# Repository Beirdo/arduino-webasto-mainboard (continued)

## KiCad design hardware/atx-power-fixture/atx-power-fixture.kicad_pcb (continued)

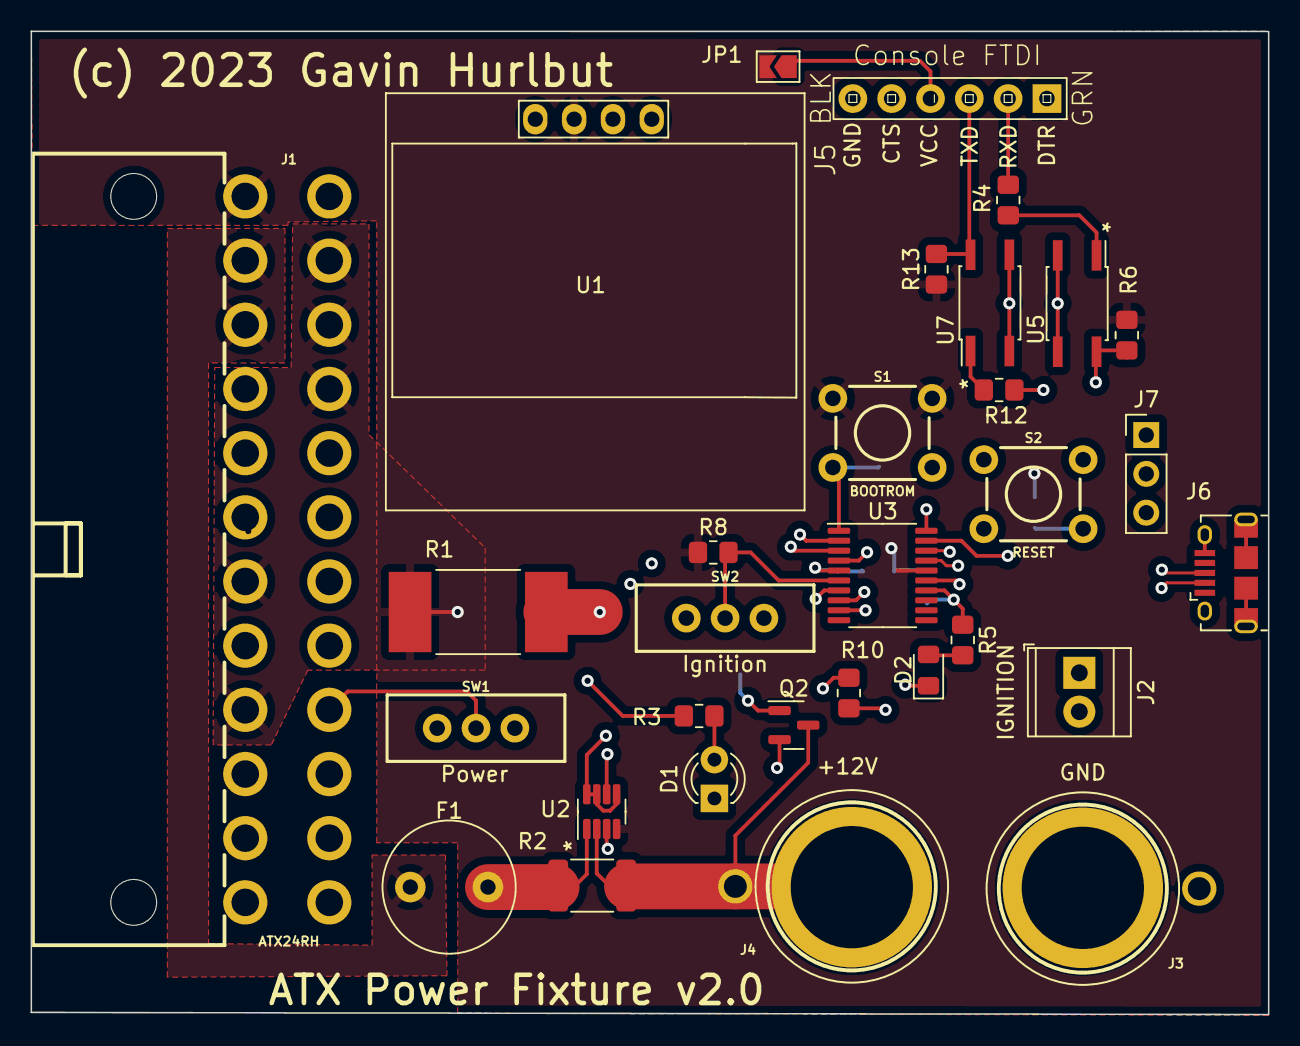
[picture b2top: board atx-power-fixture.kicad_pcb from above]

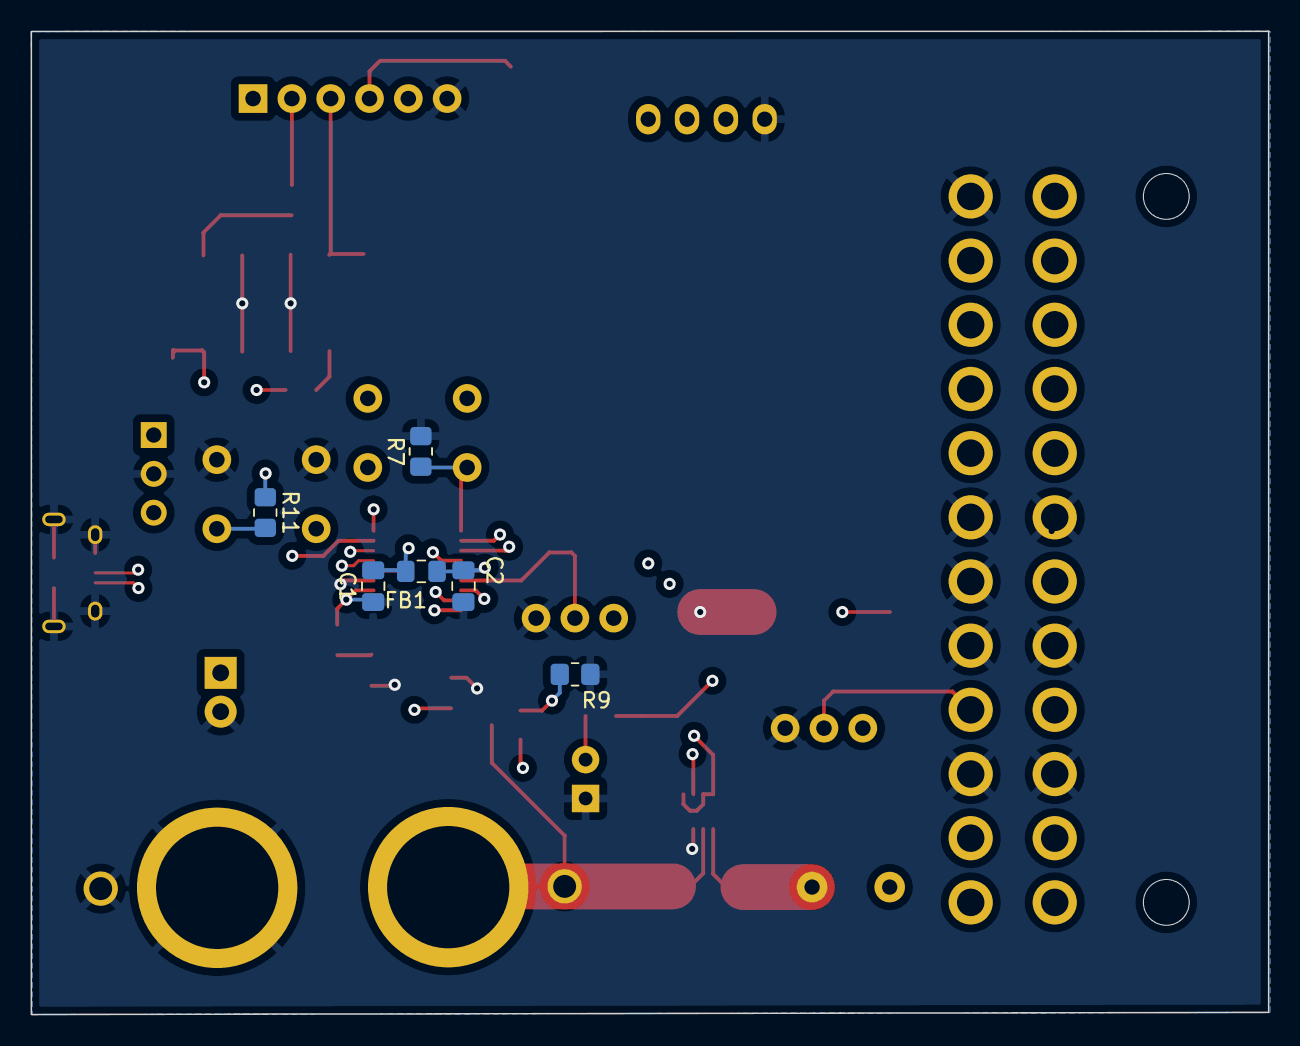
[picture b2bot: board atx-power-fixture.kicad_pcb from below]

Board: 4 copper layers, 81.0 x 64.3 mm, 37 parts (6 on the bottom side), 30 nets.

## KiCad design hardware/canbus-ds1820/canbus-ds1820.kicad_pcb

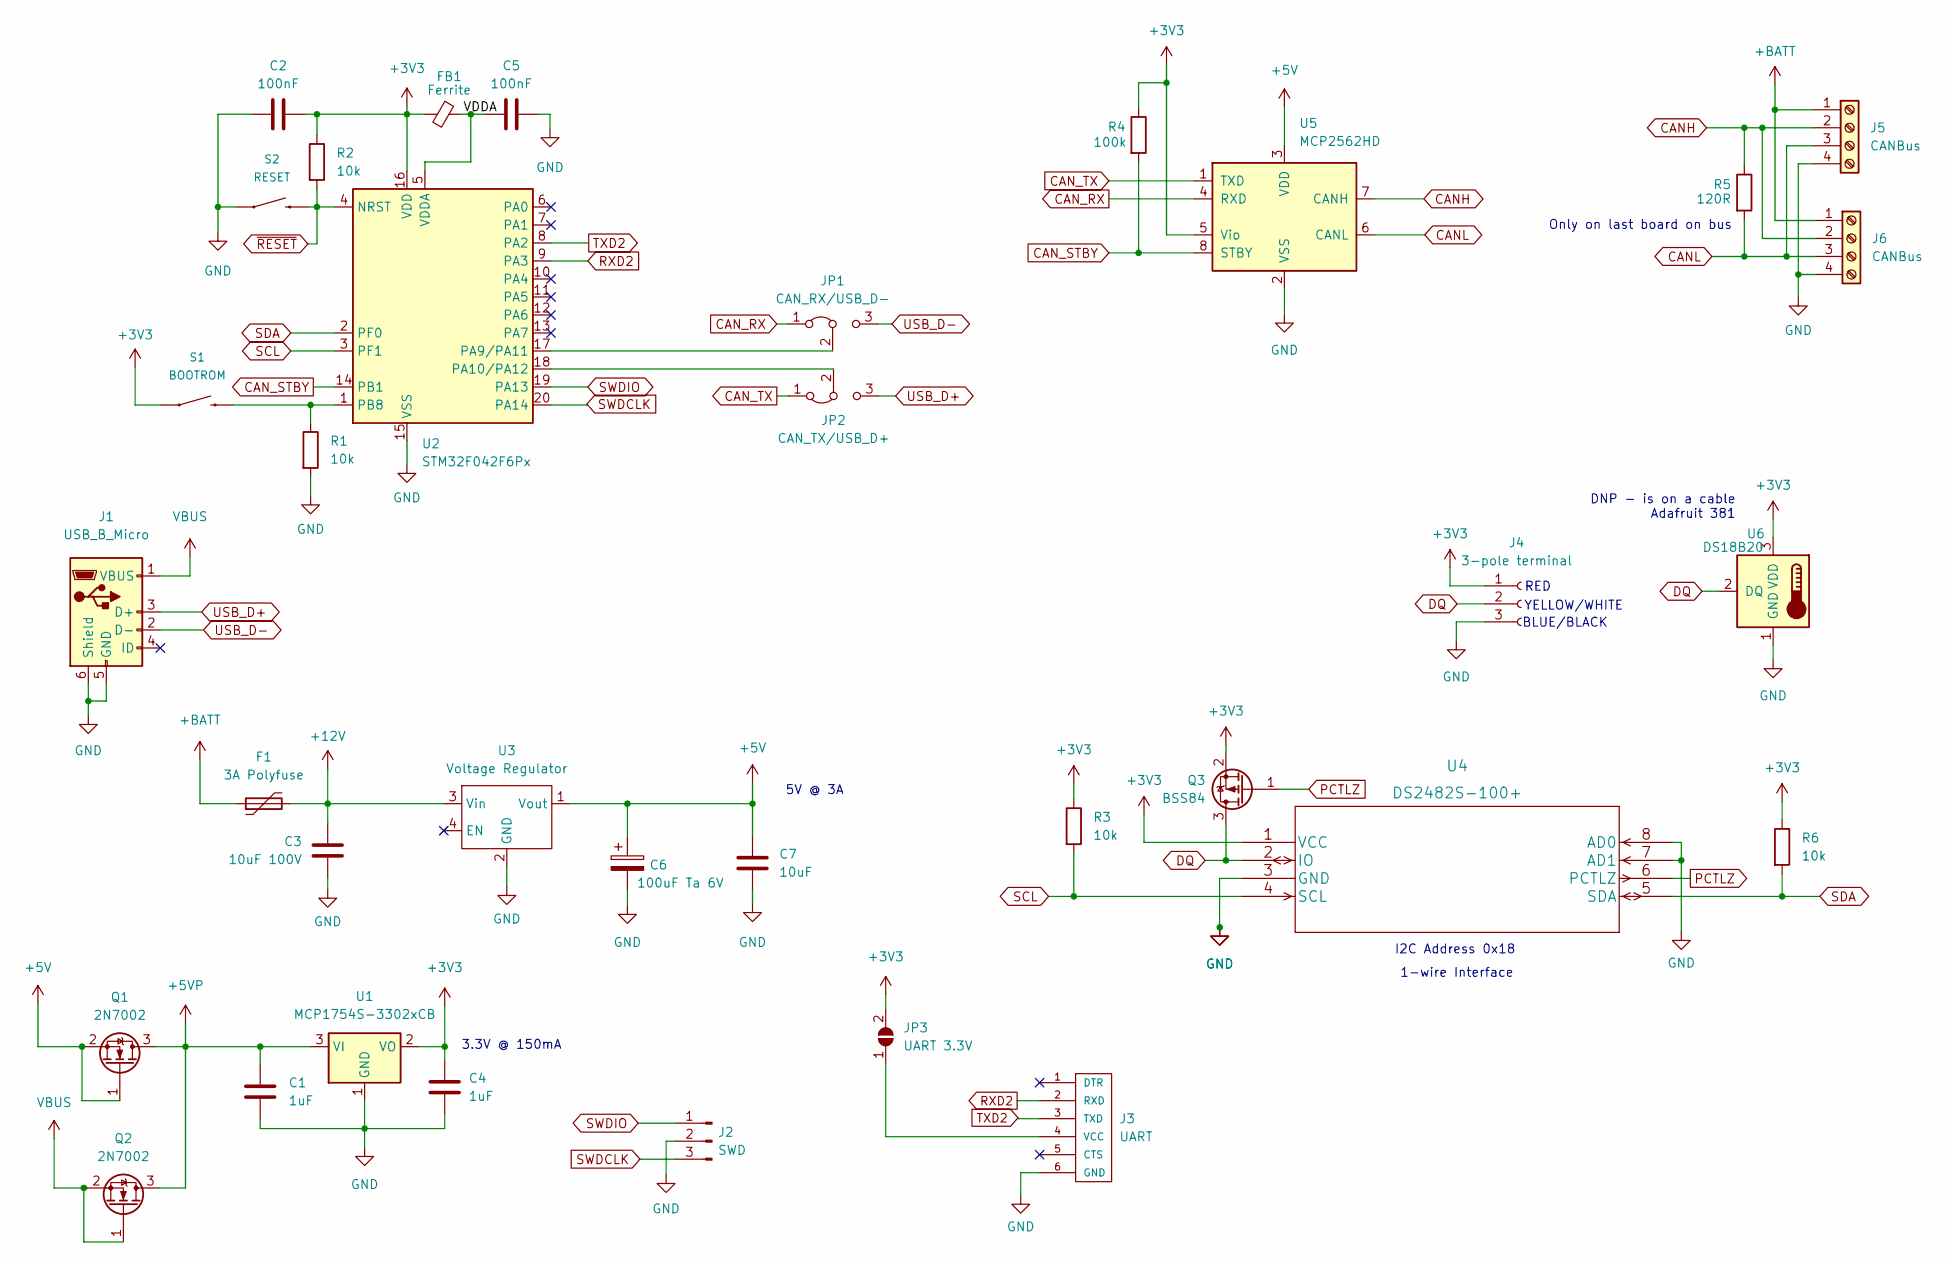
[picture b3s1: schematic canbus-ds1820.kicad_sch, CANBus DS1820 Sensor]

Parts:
C1, C4: 1uF; C_0805_2012Metric_Pad1.18x1.45mm_HandSolder
C2, C5: 100nF; C_0805_2012Metric_Pad1.18x1.45mm_HandSolder
C3: 10uF 100V; C_1210_3225Metric_Pad1.33x2.70mm_HandSolder
C6: 100uF Ta 6V; CP_EIA-3216-10_Kemet-I_Pad1.58x1.35mm_HandSolder
C7: 10uF; C_0805_2012Metric_Pad1.18x1.45mm_HandSolder
F1: 3A Polyfuse; R_1812_4532Metric_Pad1.30x3.40mm_HandSolder; Digikey F2772CT-ND
FB1: Ferrite; L_0805_2012Metric_Pad1.15x1.40mm_HandSolder
J1: USB_B_Micro; USB_Micro-B_Amphenol_10118194_Horizontal
J2: SWD; PinHeader_1x03_P2.54mm_Vertical
J3: UART; FTDI-TARGET
J4: 3-pole terminal; TerminalBlock_TE_282834-3_1x03_P2.54mm_Horizontal
J5, J6: CANBus; TerminalBlock_TE_282834-4_1x04_P2.54mm_Horizontal
JP1: CAN_RX/USB_D-; PinHeader_1x03_P2.54mm_Vertical
JP2: CAN_TX/USB_D+; PinHeader_1x03_P2.54mm_Vertical
JP3: UART 3.3V; SolderJumper-2_P1.3mm_Open_TrianglePad1.0x1.5mm
Q1, Q2: 2N7002; SOT-23
Q3: BSS84; SOT-23
R1, R2, R3, R6: 10k; R_0805_2012Metric_Pad1.20x1.40mm_HandSolder
R4: 100k; R_0805_2012Metric_Pad1.20x1.40mm_HandSolder
R5: 120R; R_0805_2012Metric_Pad1.20x1.40mm_HandSolder
S1: BOOTROM; TACTILE_SWITCH_PTH_6.0MM
S2: RESET; TACTILE_SWITCH_PTH_6.0MM
U1: MCP1754S-3302xCB; SOT-23
U2: STM32F042F6Px; TSSOP-20_4.4x6.5mm_P0.65mm
U3: Voltage Regulator; Switching_Regulator_Module
U4: DS2482S-100+; DS2482S-100&plus_
U5: MCP2562HD; SOIC-8_3.9x4.9mm_P1.27mm
U6: DS18B20; TO-92_Inline

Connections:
+3V3: C2.2, C4.1, FB1.2, J4.1, JP3.2 (B), Q3.2 (S), R2.1, R3.1, R4.1, R6.1, S1.1, U1.2 (VO), U2.16 (VDD), U4.1 (VCC), U5.5 (Vio), U6.3 (VDD)
+5V: C6.1, C7.1, Q1.1 (G), Q1.2 (S), U3.1 (Vout), U5.3 (VDD)
+5VP: C1.1, Q1.3 (D), Q2.3 (D), U1.3 (VI)
+12V: C3.1, F1.2, U3.3 (Vin)
+BATT: F1.1, J5.1, J6.1
/VDDA: C5.1, FB1.1, U2.5 (VDDA)
CANH: J5.2, J6.2, R5.1, U5.7 (CANH)
CANL: J5.3, J6.3, R5.2, U5.6 (CANL)
CAN_RX: JP1.1 (A), U5.4 (RXD)
CAN_STBY: R4.2, U2.14 (PB1), U5.8 (STBY)
CAN_TX: JP2.1 (A), U5.1 (TXD)
DQ: J4.2, Q3.3 (D), U4.2 (IO), U6.2 (DQ)
GND: C1.2, C2.1, C3.2, C4.2, C5.2, C6.2, C7.2, J1.5 (GND), J1.6 (Shield), J2.2, J3.6 (GND), J4.3, J5.4, J6.4, R1.2, S2.1, U1.1 (GND), U2.15 (VSS), U3.2 (GND), U4.3 (GND), U4.7 (AD1), U4.8 (AD0), U5.2 (VSS), U6.1 (GND)
unnamed: J3.4 (VCC), JP3.1 (A)
unnamed: JP1.2 (C), U2.17 (PA9/PA11)
unnamed: JP2.2 (C), U2.18 (PA10/PA12)
unnamed: R1.1, S1.3 (2), U2.1 (PB8)
PCTLZ: Q3.1 (G), U4.6 (PCTLZ)
RXD2: J3.2 (RXD), U2.9 (PA3)
SCL: R3.2, U2.3 (PF1), U4.4 (SCL)
SDA: R6.2, U2.2 (PF0), U4.5 (SDA)
SWDCLK: J2.3, U2.20 (PA14)
SWDIO: J2.1, U2.19 (PA13)
TXD2: J3.3 (TXD), U2.8 (PA2)
USB_D+: J1.3 (D+), JP2.3 (B)
USB_D-: J1.2 (D-), JP1.3 (B)
VBUS: J1.1 (VBUS), Q2.1 (G), Q2.2 (S)
~RESET: R2.2, S2.3 (2), U2.4 (NRST)

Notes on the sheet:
5V @ 3A
Only on last board on bus
I2C Address 0x18
BLUE/BLACK
YELLOW/WHITE
RED
1-wire Interface
DNP - is on a cable Adafruit 381
3.3V @ 150mA

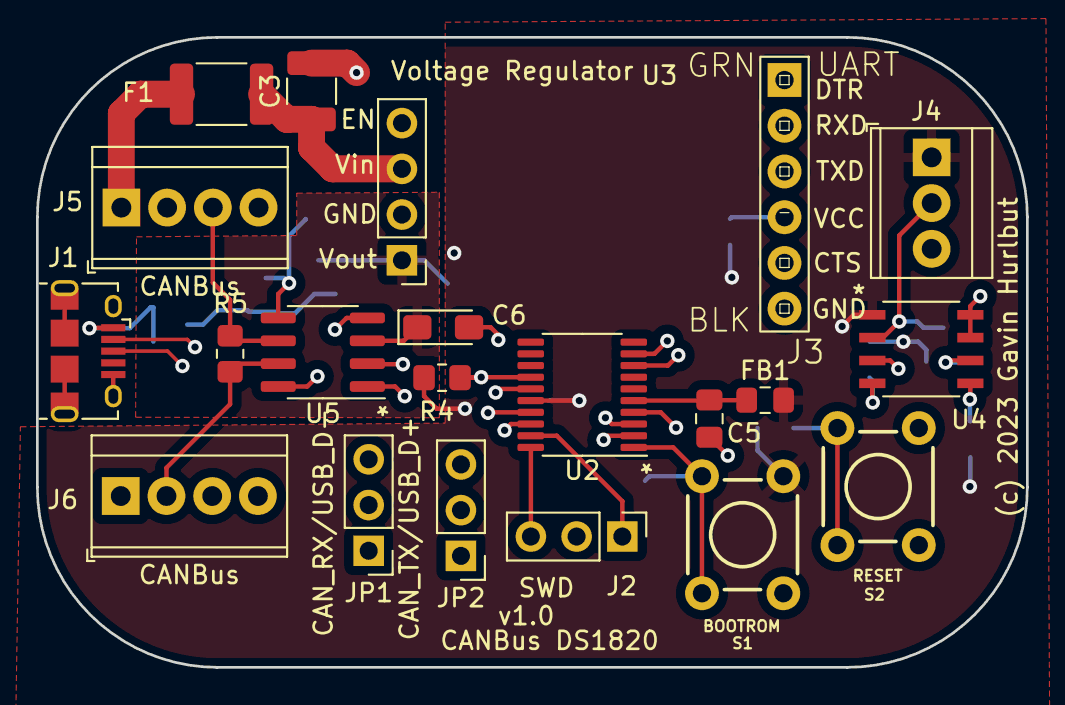
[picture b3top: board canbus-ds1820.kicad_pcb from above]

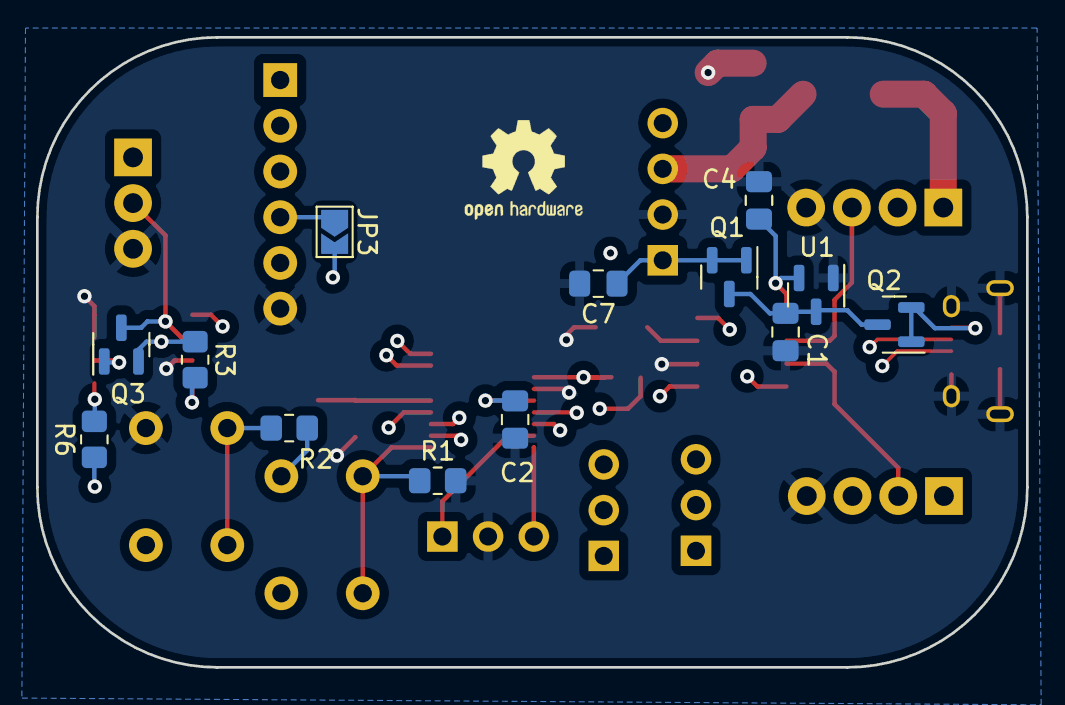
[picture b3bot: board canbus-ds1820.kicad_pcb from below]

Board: 4 copper layers, 55.0 x 35.0 mm, 35 parts (13 on the bottom side), 28 nets.

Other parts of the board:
BOARD: Altoid-Board-Outline

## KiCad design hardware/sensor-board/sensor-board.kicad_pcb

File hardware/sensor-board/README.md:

Coolant sensor:  PANW103395-395 (Digikey 570-1458-ND) inserted into:
                 https://www.amazon.com/dp/B09V6Y4ST8
	         set R6 = 10k, R4 = 0R, R7 = open

Battery voltage: set R6 = open, R4 = 49.9k 1%, R7 = 10.0k 1%

Exhaust sensor: K Type thermocouple

Ignition sensor: diode-protected input with pullup.  When ignition is on, 
                 the diode is reverse biased, and thus the input is high.
		 when ignition is on, the diode is forward biased, and the
                 input is low (around 0.7V).

Outdoors temp sensor:  DS18B20 on a cable - Adafruit part 381, connected to 
                       DS2482S-100+ 1Wire-I2C interface.

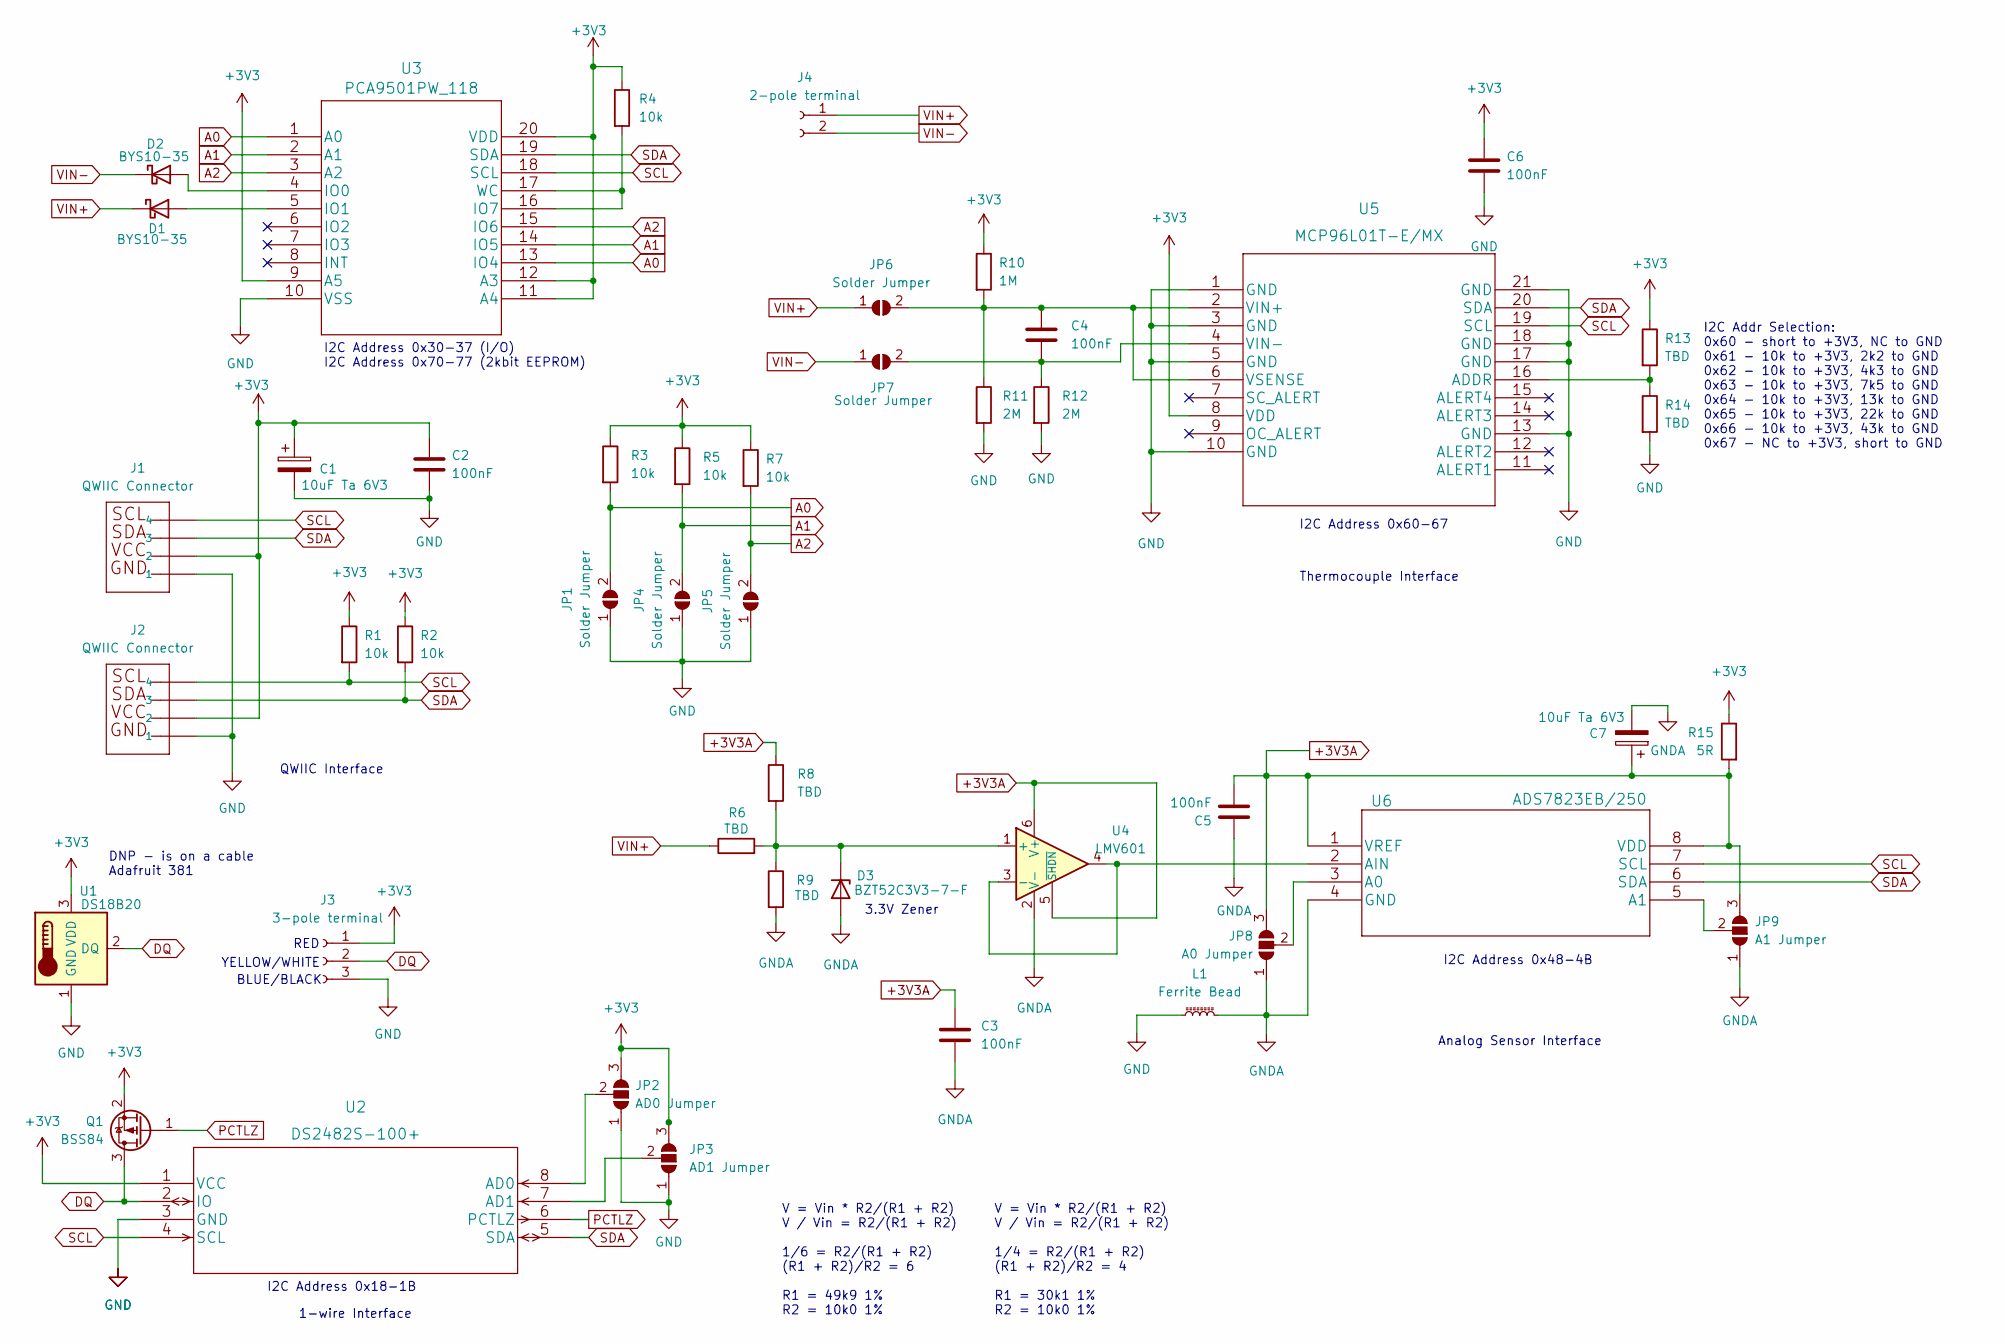
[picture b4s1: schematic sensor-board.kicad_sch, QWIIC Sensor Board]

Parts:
C1, C7: 10uF Ta 6V3; CP_EIA-3216-10_Kemet-I_Pad1.58x1.35mm_HandSolder
C2, C3, C4, C5, C6: 100nF; C_0805_2012Metric_Pad1.18x1.45mm_HandSolder
D1, D2: BYS10-35; D_SMA_Handsoldering
D3: BZT52C3V3-7-F; D_SOD-123
J1, J2: QWIIC Connector
J3: 3-pole terminal; TerminalBlock_Altech_AK300-3_P5.00mm
J4: 2-pole terminal; TerminalBlock_Altech_AK300-2_P5.00mm
JP1, JP4, JP5, JP6, JP7: Solder Jumper; SolderJumper-2_P1.3mm_Open_TrianglePad1.0x1.5mm
JP2: AD0 Jumper; SolderJumper-3_P2.0mm_Open_TrianglePad1.0x1.5mm
JP3: AD1 Jumper; SolderJumper-3_P2.0mm_Open_TrianglePad1.0x1.5mm
JP8: A0 Jumper; SolderJumper-3_P2.0mm_Open_TrianglePad1.0x1.5mm
JP9: A1 Jumper; SolderJumper-3_P2.0mm_Open_TrianglePad1.0x1.5mm
L1: Ferrite Bead; L_0805_2012Metric_Pad1.05x1.20mm_HandSolder
Q1: BSS84; SOT-23
R1, R2, R3, R4, R5, R7: 10k; R_0805_2012Metric_Pad1.20x1.40mm_HandSolder
R6, R8, R9, R13, R14: TBD; R_0805_2012Metric_Pad1.20x1.40mm_HandSolder
R10: 1M; R_0805_2012Metric_Pad1.20x1.40mm_HandSolder
R11, R12: 2M; R_0805_2012Metric_Pad1.20x1.40mm_HandSolder
R15: 5R; R_0805_2012Metric_Pad1.20x1.40mm_HandSolder
U1: DS18B20; TO-92_Inline
U2: DS2482S-100+; ds2482s-100&plus_
U3: PCA9501PW_118
U4: LMV601; SOT-363_SC-70-6
U5: MCP96L01T-E/MX; MCP96L01T-E&slash_MX
U6: ADS7823EB/250; ADS7823EB&slash_250

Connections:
+3V3: C1.1, C2.1, C6.1, J1.2, J2.2, J3.1, JP2.3 (B), JP3.3 (B), Q1.2 (S), R1.1, R2.1, R3.1, R4.1, R5.1, R7.1, R10.1, R13.1, R15.1, U1.3 (VDD), U2.1 (VCC), U3.9 (A5), U3.11 (A4), U3.12 (A3), U3.20 (VDD), U5.8 (VDD)
+3V3A: C3.2, C5.1, C7.1, JP8.3 (B), JP9.3 (B), R8.1, R15.2, U4.5 (~SHDN), U4.6 (V+), U6.1 (VREF), U6.8 (VDD)
A0: JP1.2 (B), R3.2, U3.1 (A0), U3.13 (IO4)
A1: JP4.2 (B), R5.2, U3.2 (A1), U3.14 (IO5)
A2: JP5.2 (B), R7.2, U3.3 (A2), U3.15 (IO6)
DQ: J3.2, Q1.3 (D), U1.2 (DQ), U2.2 (IO)
GND: C1.2, C2.2, C6.2, J1.1, J2.1, J3.3, JP1.1 (A), JP2.1 (A), JP3.1 (A), JP4.1 (A), JP5.1 (A), L1.1, R11.2, R12.2, R14.2, U1.1 (GND), U2.3 (GND), U3.10 (VSS), U5.1 (GND), U5.3 (GND), U5.5 (GND), U5.10 (GND), U5.13 (GND), U5.17 (GND), U5.18 (GND), U5.21 (GND)
GNDA: C3.1, C5.2, C7.2, D3.2 (A), JP8.1 (A), JP9.1 (A), L1.2, R9.2, U4.2 (V-), U6.4 (GND)
unnamed: C4.1, JP6.2 (B), R10.2, R11.1, U5.2 (VIN+), U5.6 (VSENSE)
unnamed: C4.2, JP7.2 (B), R12.1, U5.4 (VIN-)
unnamed: D3.1 (K), R6.2, R8.2, R9.1, U4.1 (+)
unnamed: JP2.2 (C), U2.8 (AD0)
unnamed: JP3.2 (C), U2.7 (AD1)
unnamed: JP8.2 (C), U6.3 (A0)
unnamed: JP9.2 (C), U6.5 (A1)
unnamed: R4.2, U3.16 (IO7), U3.17 (WC)
unnamed: R13.2, R14.1, U5.16 (ADDR)
unnamed: D2.2 (A), U3.4 (IO0)
unnamed: D1.2 (A), U3.5 (IO1)
unnamed: U4.3 (-), U4.4, U6.2 (AIN)
PCTLZ: Q1.1 (G), U2.6 (PCTLZ)
SCL: J1.4, J2.4, R1.2, U2.4 (SCL), U3.18 (SCL), U5.19 (SCL), U6.7 (SCL)
SDA: J1.3, J2.3, R2.2, U2.5 (SDA), U3.19 (SDA), U5.20 (SDA), U6.6 (SDA)
VIN+: D1.1 (K), J4.1, JP6.1 (A), R6.1
VIN-: D2.1 (K), J4.2, JP7.1 (A)

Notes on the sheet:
I2C Address 0x48-4B
YELLOW/WHITE
DNP - is on a cable Adafruit 381
BLUE/BLACK
V = Vin * R2/(R1 + R2) V / Vin = R2/(R1 + R2) 1/6 = R2/(R1 + R2) (R1 + R2)/R2 = 6 R1 = 49k9 1% R2 = 10k0 1%
I2C Address 0x30-37 (I/O) I2C Address 0x70-77 (2kbit EEPROM)
RED
I2C Address 0x18-1B
3.3V Zener
Thermocouple Interface
Analog Sensor Interface
QWIIC Interface
I2C Addr Selection: 0x60 - short to +3V3, NC to GND 0x61 - 10k to +3V3, 2k2 to GND 0x62 - 10k to +3V3, 4k3 to GND 0x63 - 10k to +3V3, 7k5 to GND 0x64 - 10k to +3V3, 13k to GND 0x65 - 10k to +3V3, 22k to GND 0x66 - 10k to +3V3, 43k to GND 0x67 - NC to +3V3, short to GND
V = Vin * R2/(R1 + R2) V / Vin = R2/(R1 + R2) 1/4 = R2/(R1 + R2) (R1 + R2)/R2 = 4 R1 = 30k1 1% R2 = 10k0 1%
1-wire Interface
I2C Address 0x60-67

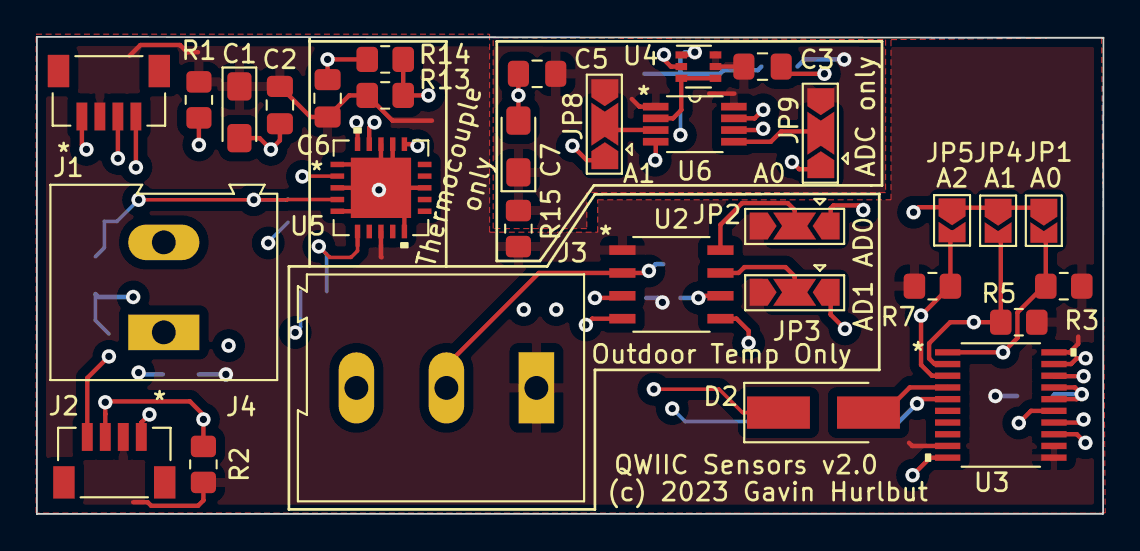
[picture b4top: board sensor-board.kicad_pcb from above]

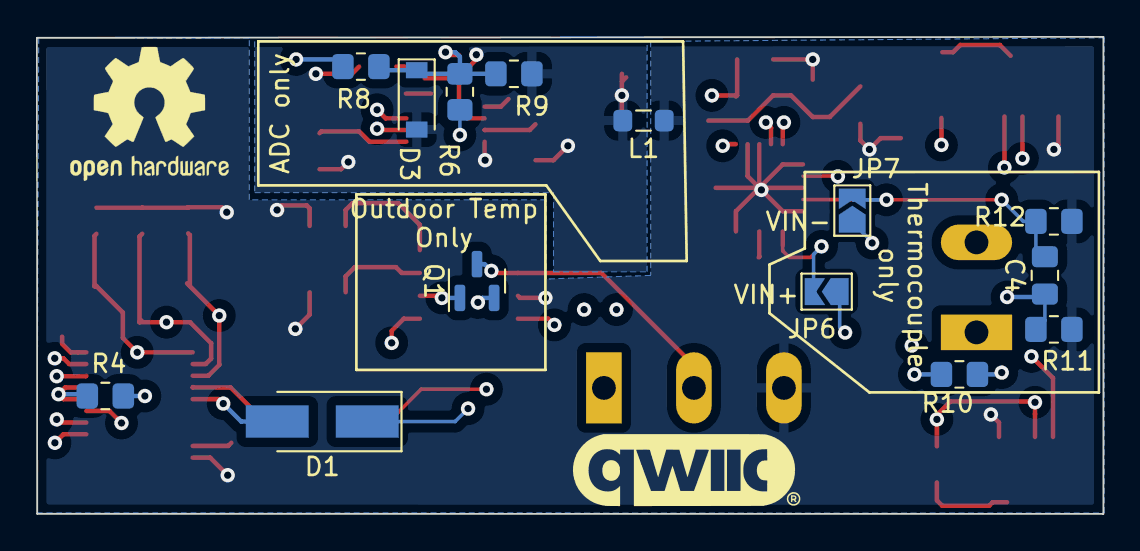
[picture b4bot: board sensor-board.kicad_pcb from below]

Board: 4 copper layers, 59.2 x 26.5 mm, 45 parts (14 on the bottom side), 25 nets.

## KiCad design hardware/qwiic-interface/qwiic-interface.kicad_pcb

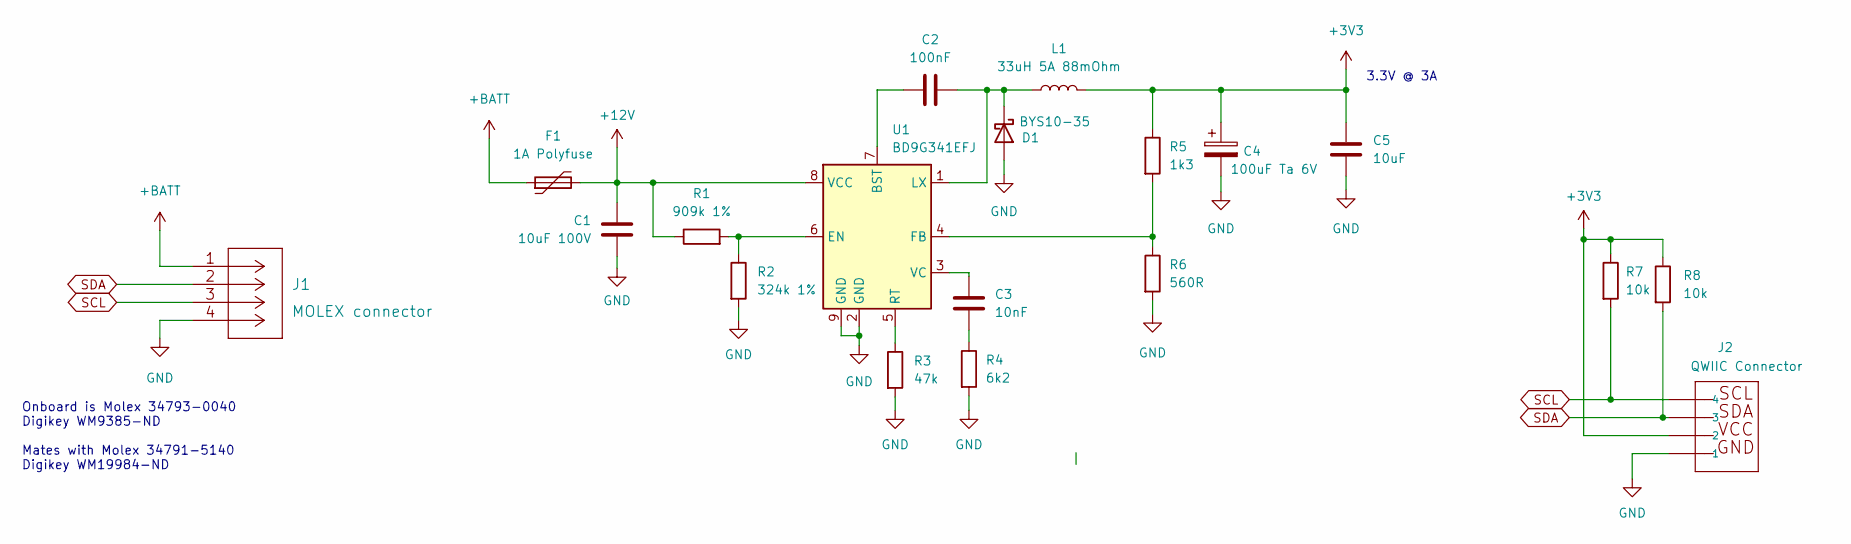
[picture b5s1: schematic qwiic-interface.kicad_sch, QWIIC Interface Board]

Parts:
C1: 10uF 100V; C_1210_3225Metric_Pad1.33x2.70mm_HandSolder
C2: 100nF; C_0805_2012Metric_Pad1.18x1.45mm_HandSolder
C3: 10nF; C_0805_2012Metric_Pad1.18x1.45mm_HandSolder
C4: 100uF Ta 6V; CP_EIA-3216-10_Kemet-I_Pad1.58x1.35mm_HandSolder
C5: 10uF; C_0805_2012Metric_Pad1.18x1.45mm_HandSolder
D1: BYS10-35; D_SMA_Handsoldering
F1: 1A Polyfuse; R_0805_2012Metric_Pad1.20x1.40mm_HandSolder; Digikey F2772CT-ND
J1: MOLEX connector; 347930040
J2: QWIIC Connector
L1: 33uH 5A 88mOhm; PM4346.333NLT; Digikey 553-PM4346.333NLTTR-ND
R1: 909k 1%; R_0805_2012Metric_Pad1.20x1.40mm_HandSolder
R2: 324k 1%; R_0805_2012Metric_Pad1.20x1.40mm_HandSolder
R3: 47k; R_0805_2012Metric_Pad1.20x1.40mm_HandSolder
R4: 6k2; R_0805_2012Metric_Pad1.20x1.40mm_HandSolder
R5: 1k3; R_0805_2012Metric_Pad1.20x1.40mm_HandSolder
R6: 560R; R_0805_2012Metric_Pad1.20x1.40mm_HandSolder
R7, R8: 10k; R_0805_2012Metric_Pad1.20x1.40mm_HandSolder
U1: BD9G341EFJ; HTSOP-8-1EP_3.9x4.9mm_P1.27mm_EP2.4x3.2mm_ThermalVias

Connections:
+3V3: C4.1, C5.1, J2.2, L1.2, R5.1, R7.1, R8.1
+12V: C1.1, F1.2, R1.1, U1.8 (VCC)
+BATT: F1.1, J1.1
GND: C1.2, C4.2, C5.2, D1.2 (A), J1.4, J2.1, R2.2, R3.2, R4.2, R6.2, U1.2 (GND), U1.9 (GND)
unnamed: C2.1, U1.7 (BST)
unnamed: C2.2, D1.1 (K), L1.1, U1.1 (LX)
unnamed: C3.1, U1.3 (VC)
unnamed: C3.2, R4.1
unnamed: R1.2, R2.1, U1.6 (EN)
unnamed: R3.1, U1.5 (RT)
unnamed: R5.2, R6.1, U1.4 (FB)
SCL: J1.3, J2.4, R7.2
SDA: J1.2, J2.3, R8.2

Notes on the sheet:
Onboard is Molex 34793-0040 Digikey WM9385-ND Mates with Molex 34791-5140 Digikey WM19984-ND
3.3V @ 3A

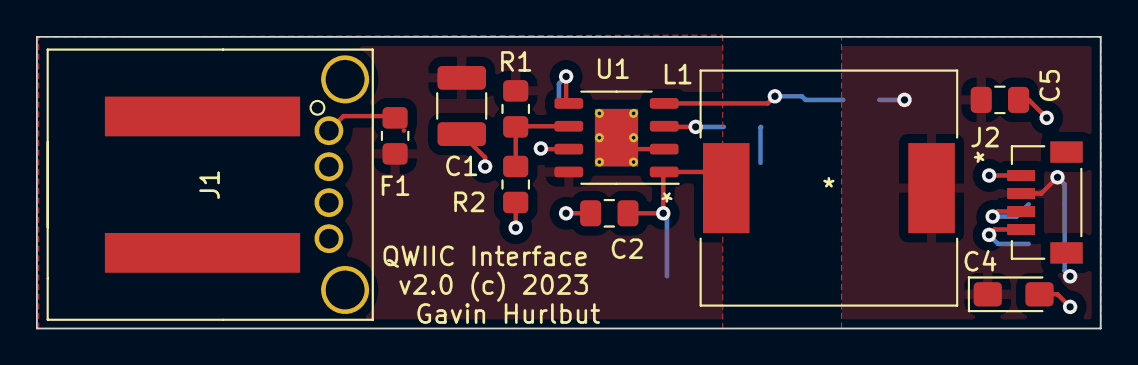
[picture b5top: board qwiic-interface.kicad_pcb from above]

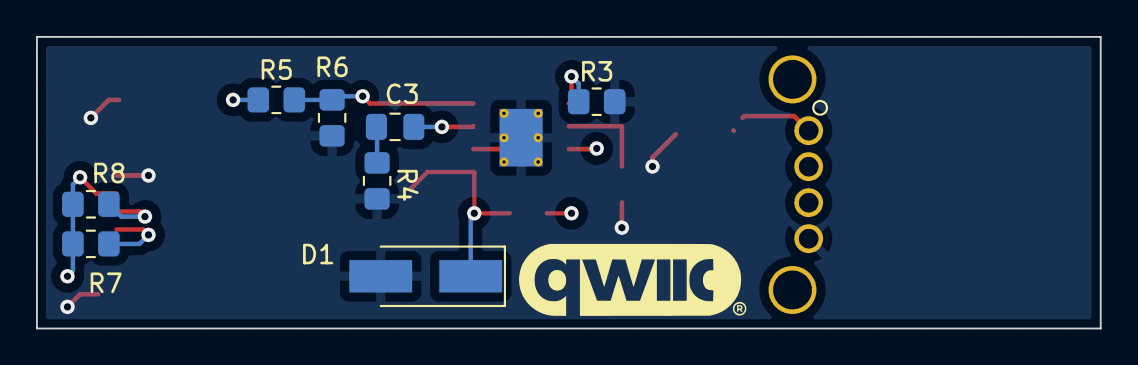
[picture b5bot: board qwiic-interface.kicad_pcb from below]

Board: 4 copper layers, 59.1 x 16.2 mm, 19 parts (8 on the bottom side), 13 nets.

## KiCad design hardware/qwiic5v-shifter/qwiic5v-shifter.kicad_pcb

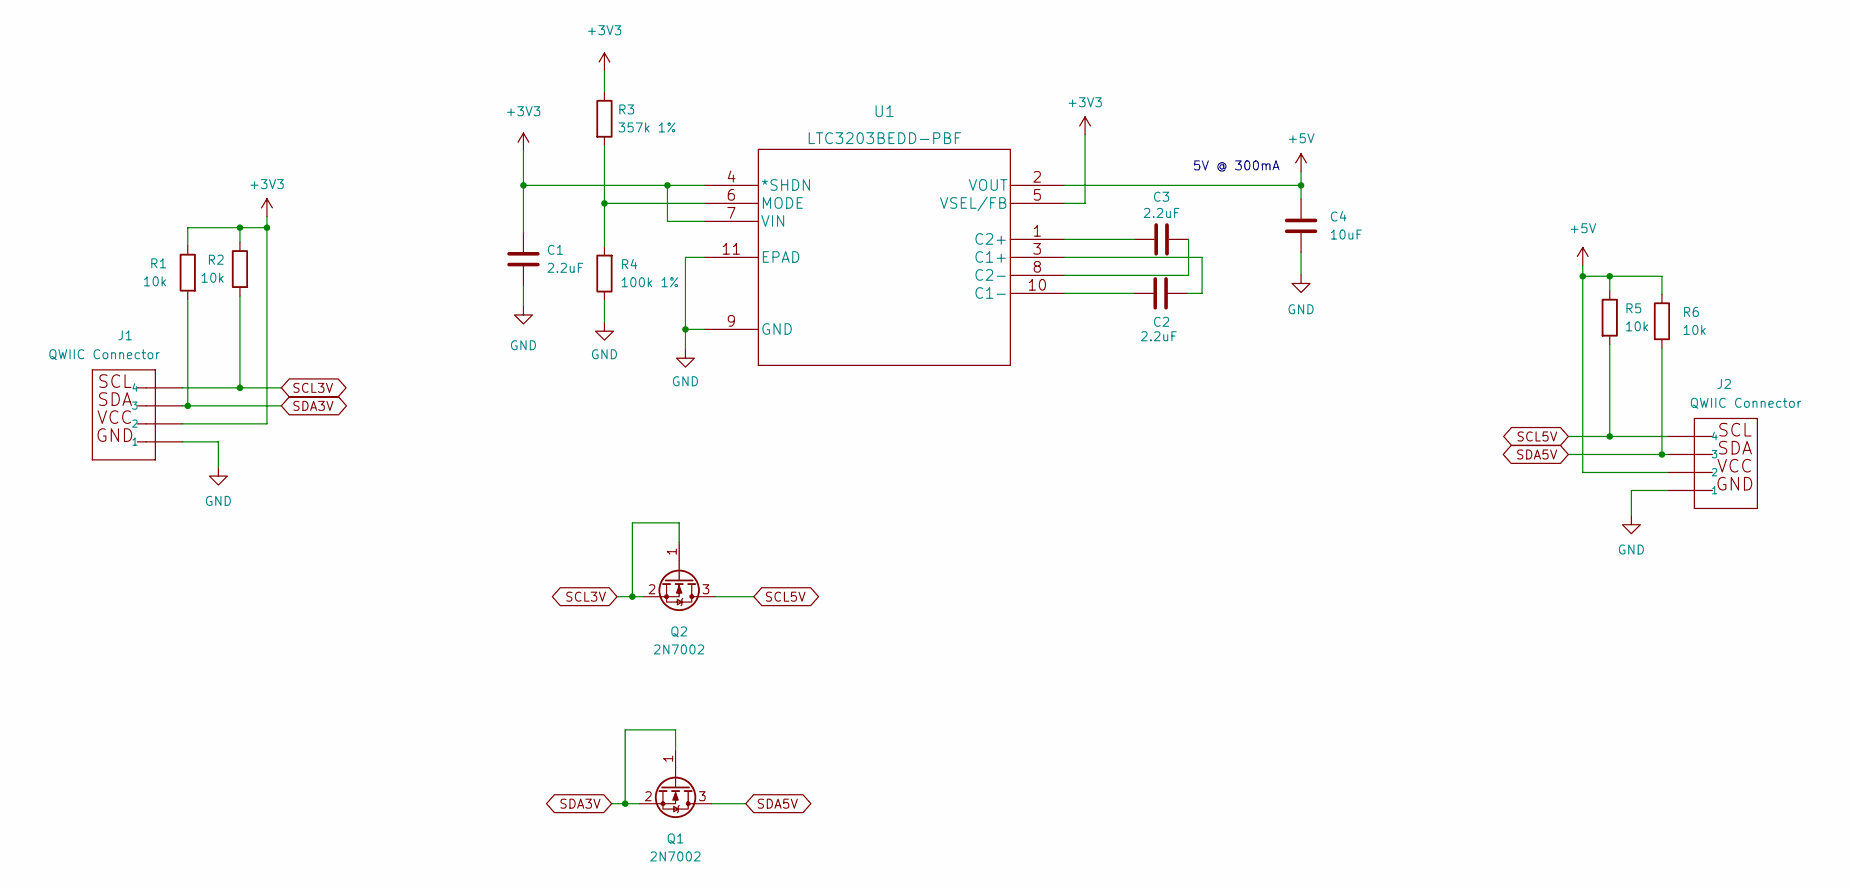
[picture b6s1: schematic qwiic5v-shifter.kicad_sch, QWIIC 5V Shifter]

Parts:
C1, C2, C3: 2.2uF; C_0805_2012Metric_Pad1.18x1.45mm_HandSolder
C4: 10uF; C_0805_2012Metric_Pad1.18x1.45mm_HandSolder
J1, J2: QWIIC Connector
Q1, Q2: 2N7002; SOT-23
R1, R2, R5, R6: 10k; R_0805_2012Metric_Pad1.20x1.40mm_HandSolder
R3: 357k 1%; R_0805_2012Metric_Pad1.20x1.40mm_HandSolder
R4: 100k 1%; R_0805_2012Metric_Pad1.20x1.40mm_HandSolder
U1: LTC3203BEDD-PBF

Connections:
+3V3: C1.1, J1.2, R1.1, R2.1, R3.1, U1.4 (*SHDN), U1.5 (VSEL/FB), U1.7 (VIN)
+5V: C4.1, J2.2, R5.1, R6.1, U1.2 (VOUT)
GND: C1.2, C4.2, J1.1, J2.1, R4.1, U1.9 (GND), U1.11 (EPAD)
unnamed: C2.1, U1.10 (C1-)
unnamed: C2.2, U1.3 (C1+)
unnamed: C3.1, U1.1 (C2+)
unnamed: C3.2, U1.8 (C2-)
unnamed: R3.2, R4.2, U1.6 (MODE)
SCL3V: J1.4, Q2.1 (G), Q2.2 (S), R2.2
SCL5V: J2.4, Q2.3 (D), R5.2
SDA3V: J1.3, Q1.1 (G), Q1.2 (S), R1.2
SDA5V: J2.3, Q1.3 (D), R6.2

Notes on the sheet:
5V @ 300mA

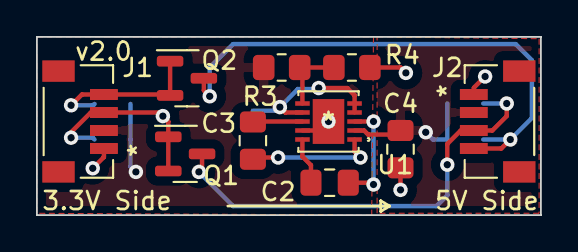
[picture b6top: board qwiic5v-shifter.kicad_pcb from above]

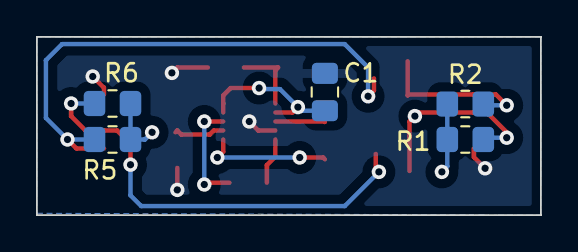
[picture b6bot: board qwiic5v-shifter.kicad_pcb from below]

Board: 2 copper layers, 28.0 x 9.9 mm, 15 parts (5 on the bottom side), 12 nets.

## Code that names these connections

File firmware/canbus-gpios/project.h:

#ifndef __project_h_
#define __project_h_

#include <Beirdo-Utilities.h>

#include "internal_gpio.h"

// Serial2 -> Console
#ifdef PIN_SERIAL2_TX
#undef PIN_SERIAL2_TX
#endif

#ifdef PIN_SERIAL2_RX
#undef PIN_SERIAL2_RX
#endif


#define PIN_START_RUN         0   // PA_0
#define PIN_IGNITION_SENSE    1   // PA_1
#define PIN_USART2_TX         2   // PA_2
#define PIN_USART2_RX         3   // PA_3
#define PIN_EMERGENCY_STOP    4   // PA_4
#define PIN_SWDIO             10  // PA_13
#define PIN_SWDCLK            11  // PA_14
#define PIN_CAN_EN            12  // PB_1
#define PIN_BOOTROM_SEL       13  // PB_8
#define PIN_CAN_RX            16  // PA_11_R
#define PIN_CAN_TX            17  // PA_12_R


extern InternalGPIOSensor startRunSensor;
extern InternalGPIOSensor ignitionSenseSensor;
extern InternalGPIOSensor emergencyStopSensor;

#endif
